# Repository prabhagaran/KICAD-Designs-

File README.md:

# KICAD-Designs-
All About designing Micro controller based Development Boards

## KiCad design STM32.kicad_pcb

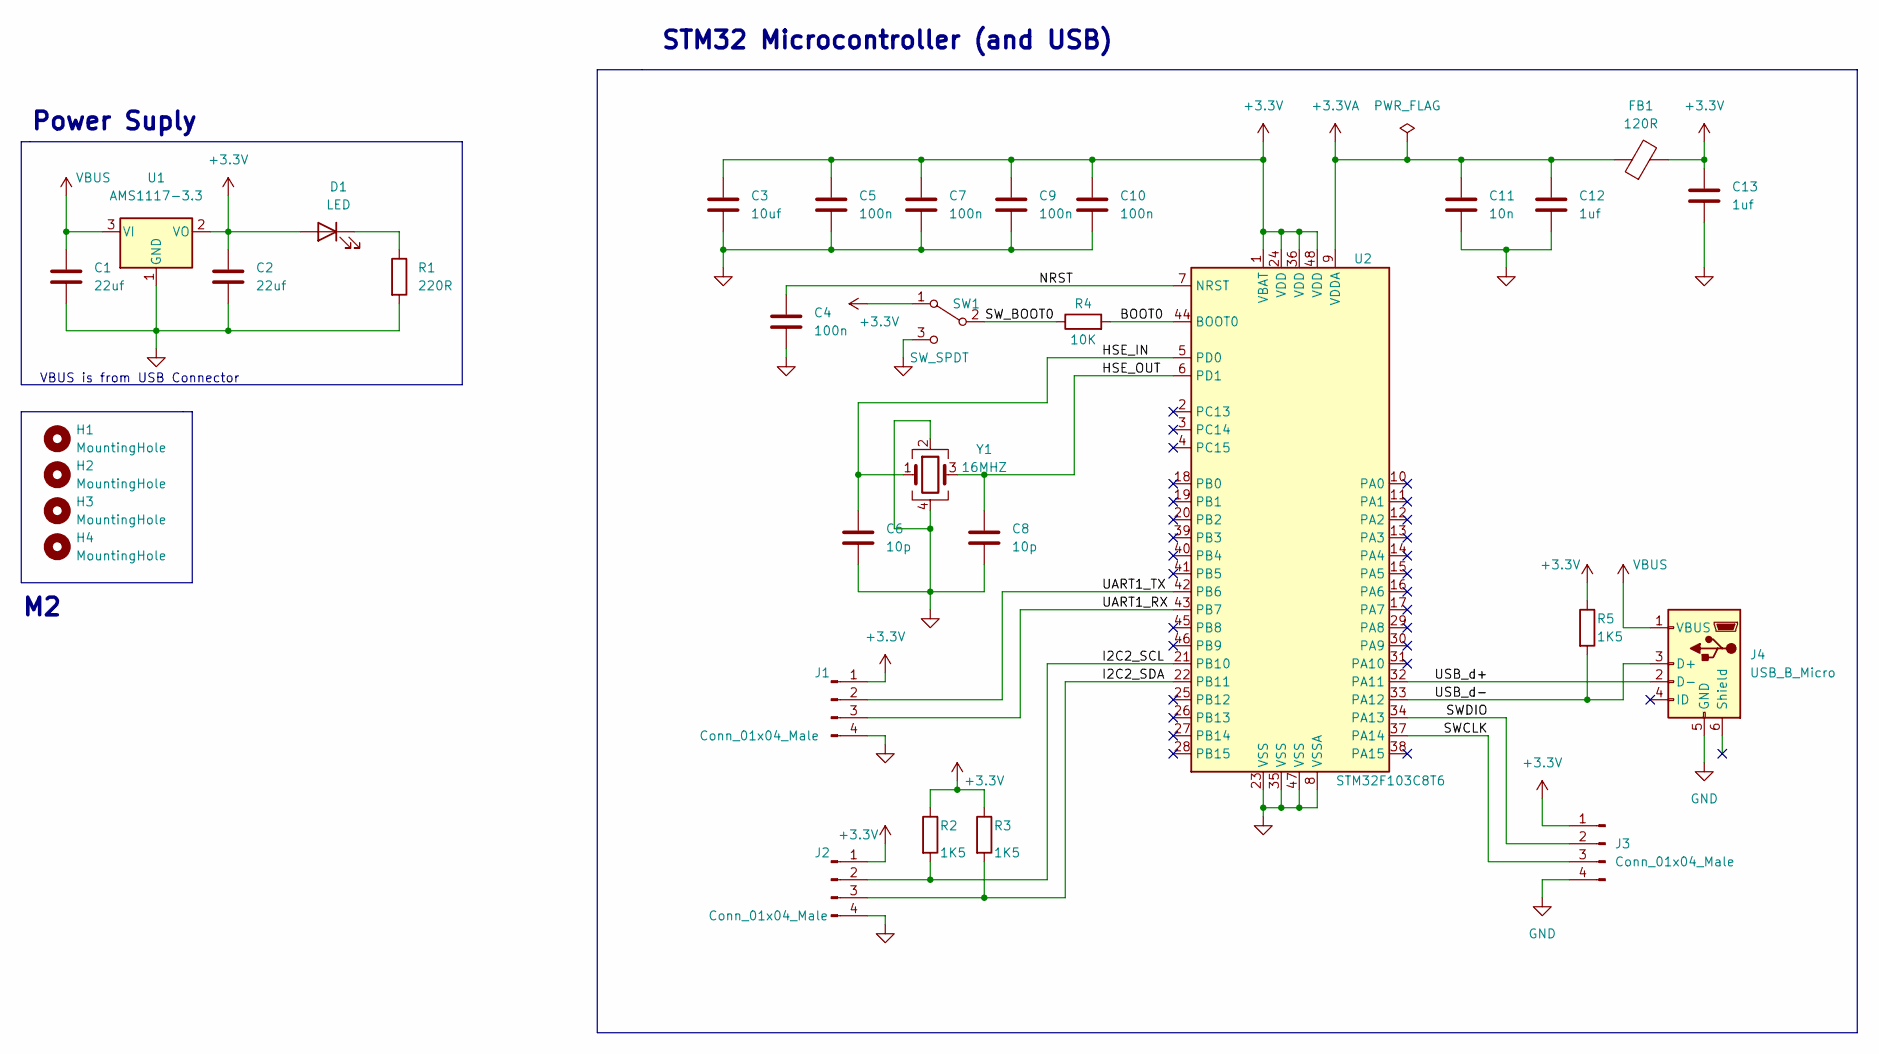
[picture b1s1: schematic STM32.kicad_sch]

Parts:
C1, C2: 22uf; C_0805_2012Metric
C3: 10uf; C_0603_1608Metric
C4, C5, C7: 100n; C_0402_1005Metric
C6, C8: 10p; C_0402_1005Metric
C9, C10: 100n; C_0603_1608Metric
C11: 10n; C_0402_1005Metric
C12, C13: 1uf; C_0402_1005Metric
D1: LED; LED_0603_1608Metric
FB1: 120R; L_0603_1608Metric
H1, H2, H3, H4: MountingHole; MountingHole_2.2mm_M2
J1, J2, J3: Conn_01x04_Male; PinHeader_1x04_P2.54mm_Vertical
J4: USB_B_Micro; USB_Micro-B_Wuerth_629105150521
R1: 220R; R_0603_1608Metric
R2, R3, R5: 1K5; R_0603_1608Metric
R4: 10K; R_0603_1608Metric
SW1: SW_SPDT; SW_SP3T_PCM13
U1: AMS1117-3.3; SOT-223-3_TabPin2
U2: STM32F103C8T6; LQFP-48_7x7mm_P0.5mm
Y1: 16MHZ; Crystal_SMD_3225-4Pin_3.2x2.5mm

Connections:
+3.3VA: C11.1, C12.1, FB1.1, U2.9 (VDDA)
+3V3: C2.1, C3.1, C5.1, C7.1, C9.1, C10.1, C13.1, D1.2 (A), FB1.2, J1.1, J2.1, J3.1, R2.1, R3.1, R5.1, SW1.1 (A), U1.2 (VO), U2.1 (VBAT), U2.24 (VDD), U2.36 (VDD), U2.48 (VDD)
/BOOT0: R4.2, U2.44 (BOOT0)
/HSE_IN: C6.1, U2.5 (PD0), Y1.1
/HSE_OUT: C8.1, U2.6 (PD1), Y1.3
/I2C2_SCL: J2.2, R2.2, U2.21 (PB10)
/I2C2_SDA: J2.3, R3.2, U2.22 (PB11)
/NRST: C4.1, U2.7 (NRST)
/SWCLK: J3.3, U2.37 (PA14)
/SWDIO: J3.2, U2.34 (PA13)
/SW_BOOT0: R4.1, SW1.2 (B)
/UART1_RX: J1.3, U2.43 (PB7)
/UART1_TX: J1.2, U2.42 (PB6)
/USB_d+: J4.2 (D-), U2.32 (PA11)
/USB_d-: J4.3 (D+), R5.2, U2.33 (PA12)
GND: C1.2, C2.2, C3.2, C4.2, C5.2, C6.2, C7.2, C8.2, C9.2, C10.2, C11.2, C12.2, C13.2, J1.4, J2.4, J3.4, J4.5 (GND), R1.2, SW1.3 (C), U1.1 (GND), U2.8 (VSSA), U2.23 (VSS), U2.35 (VSS), U2.47 (VSS), Y1.2, Y1.4
unnamed: D1.1 (K), R1.1
VBUS: C1.1, J4.1 (VBUS), U1.3 (VI)

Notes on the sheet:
Power Suply
VBUS is from USB Connector
STM32 Microcontroller (and USB)

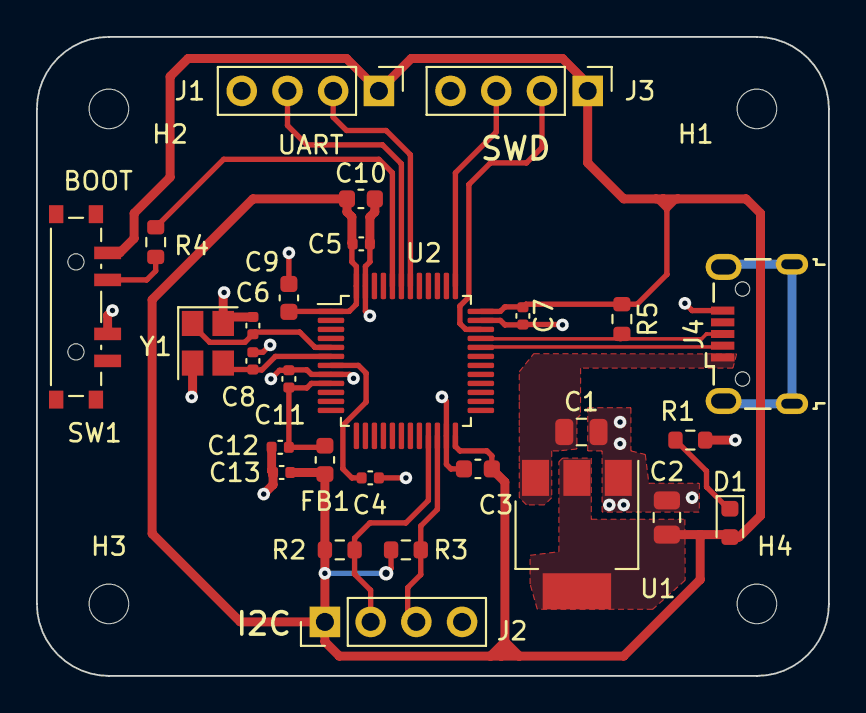
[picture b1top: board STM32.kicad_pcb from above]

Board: 2 copper layers, 44.0 x 35.5 mm, 32 parts (0 on the bottom side), 18 nets.
